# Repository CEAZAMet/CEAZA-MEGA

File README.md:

# CEAZA Mega   [![Badge License]][License]

*A reliable & expandable low power data <br>
logger for scientists, based on the Arduino.*

<br>
<br>

<div align = center>

</div>

<br>
<br>

## What It Is

Is a new simple, robust and expandable datalogger Arduino derivative board based in typical maker’s community integrations.  The board was designed and implemented taking into account requirements as low consumption, expandability and integration. Different tests where made so reliability in low temperatures and low energy needs are satisfied. 
Is expected that the scientific community can add this board to their tool set, as this board solves the energy problem and present an easy transition from handmade logger integrations.

CEAZA mega board integrate:
- ATMEGA2560 8-bit microcontroller
- Arduino mega 2560 bootloader for easy Arduino Ide compatibility
- A real time clock (RTC)
- A microSD card socket for data storage
- USB/Serial driver connected to UART0 for program as an Arduino mega or computer serial communication
- Serial RS-232 driver (connected to UART1) 
- Controlled high frequency (2MHz) step down switching regulator MP2451DT-LF-Z configured to deliver 5V and up to 600mA for external sensor
- Built in 10Kohm NTC thermistor for PCB temperature monitoring
- Power source system voltage monitor
- Terminal for direct connection with DS18B20 1-wire digittal temperature sensor
- 3 LEDs on board and external duplicate conection for two of those LEDs
- an ISCP terminal to program with external programer
- 3 expansion terminal for direct wires soldering or easy plug/unplug expansion boards for CEAZA MEGA

<br>

Furthermore, all integrated devices, except the main **MCU** <br>
uses a firmware controlled switched power supply in order <br>
to optimize de power consumption.

## Documentation

A comprehensive documentation for well understand, use <br>
or modify the **CEAZA MEGA** board is available in our Wiki. 

Additionally we share our schematic <br>
diagrams and Arduino example codes.

<br>
<br>

## Quickstart guide

1.  Connect a `6.5 - 14V` DC power supply.

2.  Connect the **CEAZA MEGA** main board to <br>
    the host PC with he mini-USB connector.

3.  Open the Arduino IDE.

4.  Select the Arduino Mega board <br>
    and the corresponding COM port.

5.  Open any of example sketches.

6.  Upload to the board.

<br>
<br>

## Contact & Support

For all kinds of inquiries, please contact me to <br>
my e-mail address: adrian.gallardo@ceaza.cl

<br>
<br>

## Contributing

You are welcome to contribute to the development <br>
or improvement of **CEAZA MEGA** hardware design <br>
or example application codes.

Feel free to submit a new pull request via **GitHub**.

<br>
<br>

## Academic Context

A paper with more details and performed tests was shown in **[DOI]**. 

<br>
<br>

## Disclaimer

Use **CEAZA MEGA** board and examples code at your own risk. <br>
We do not encourage any malicious use of our board.

<br>

<!----------------------------------------------------------------------------->

[Badge License]: https://img.shields.io/badge/License-MIT-yellow.svg?style=for-the-badge

[DOI]: http://doi.org/10.11591/ijres.v11.i2.pp175-187

[Preview]: Images/CM_PINOUT.PNG
[License]: LICENSE

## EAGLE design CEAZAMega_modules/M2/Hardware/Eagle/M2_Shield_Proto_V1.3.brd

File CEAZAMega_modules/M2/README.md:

# Welcome to CEAZA-M2!
Prototyping board for CEAZA MEGA system.

# What is the CEAZA-M2?
Is a prototyping board with a firmware controlled +5V dedicated step-down power supply and controlled Vin pin for CEAZA MEGA system.
The board give you access to some pins as a PCB breadboard format, ready to solder any module or device.
Furthermore the board have a duplicate I/O expansion terminals to give you direct access to any of its pins.
Whith CEAZA M2 board you can easyly integrate any device to CEAZA MEGA system without any other customized board.

## Documentation
A comprehensive documentation for well undertand, use or modify the CEAZA M2 board is available in our Wiki. In adition, we share with you the schematics diagrams, adns Arduino example codes.

## Quickstart guide
Plan your electronic conection to your device, solder the necesay wires to connect your devices in the M2 board.
Install the M2 board in the CEAZA MEGA's bottom, make certain connection throuhg the boards by three 2 x 10 pin header terminals is rigth. Plug the battery and solar panel cables in the respective board terminal. be careful to avoid swap both plugs, due they are the same type of terminals. Connect the CEAZA MEGA main board system to the host PC by mini-USB connector, open the Arduino ide software, select the Arduino Mega board and the correspondign COM port.
Open any of examples scketches and upload to the board.
### WARNING!
Be careful with your breadboard conections due exist a posibility of a shortcircuit of the power supply acces in the breadboard. 
A 1A PTC Resettable fuse is placed in the main electric supply to the board (VIN pin od I/O expansion terminal) for extra electric protection.

# Contact and support
For all kinds of inquiries, please contact me to my e-mail address: adrian.gallardo@ceaza.cl

# Contributing
You are welcome to contribute to the development or improvement of M2 hardware design or example application codes. Feel free to submit a new pull request via github.

# Academic Context

# Licensing

# Disclaimer
Use M2 board and examples code at your own risk. We do not encourage any malicious use of our board.

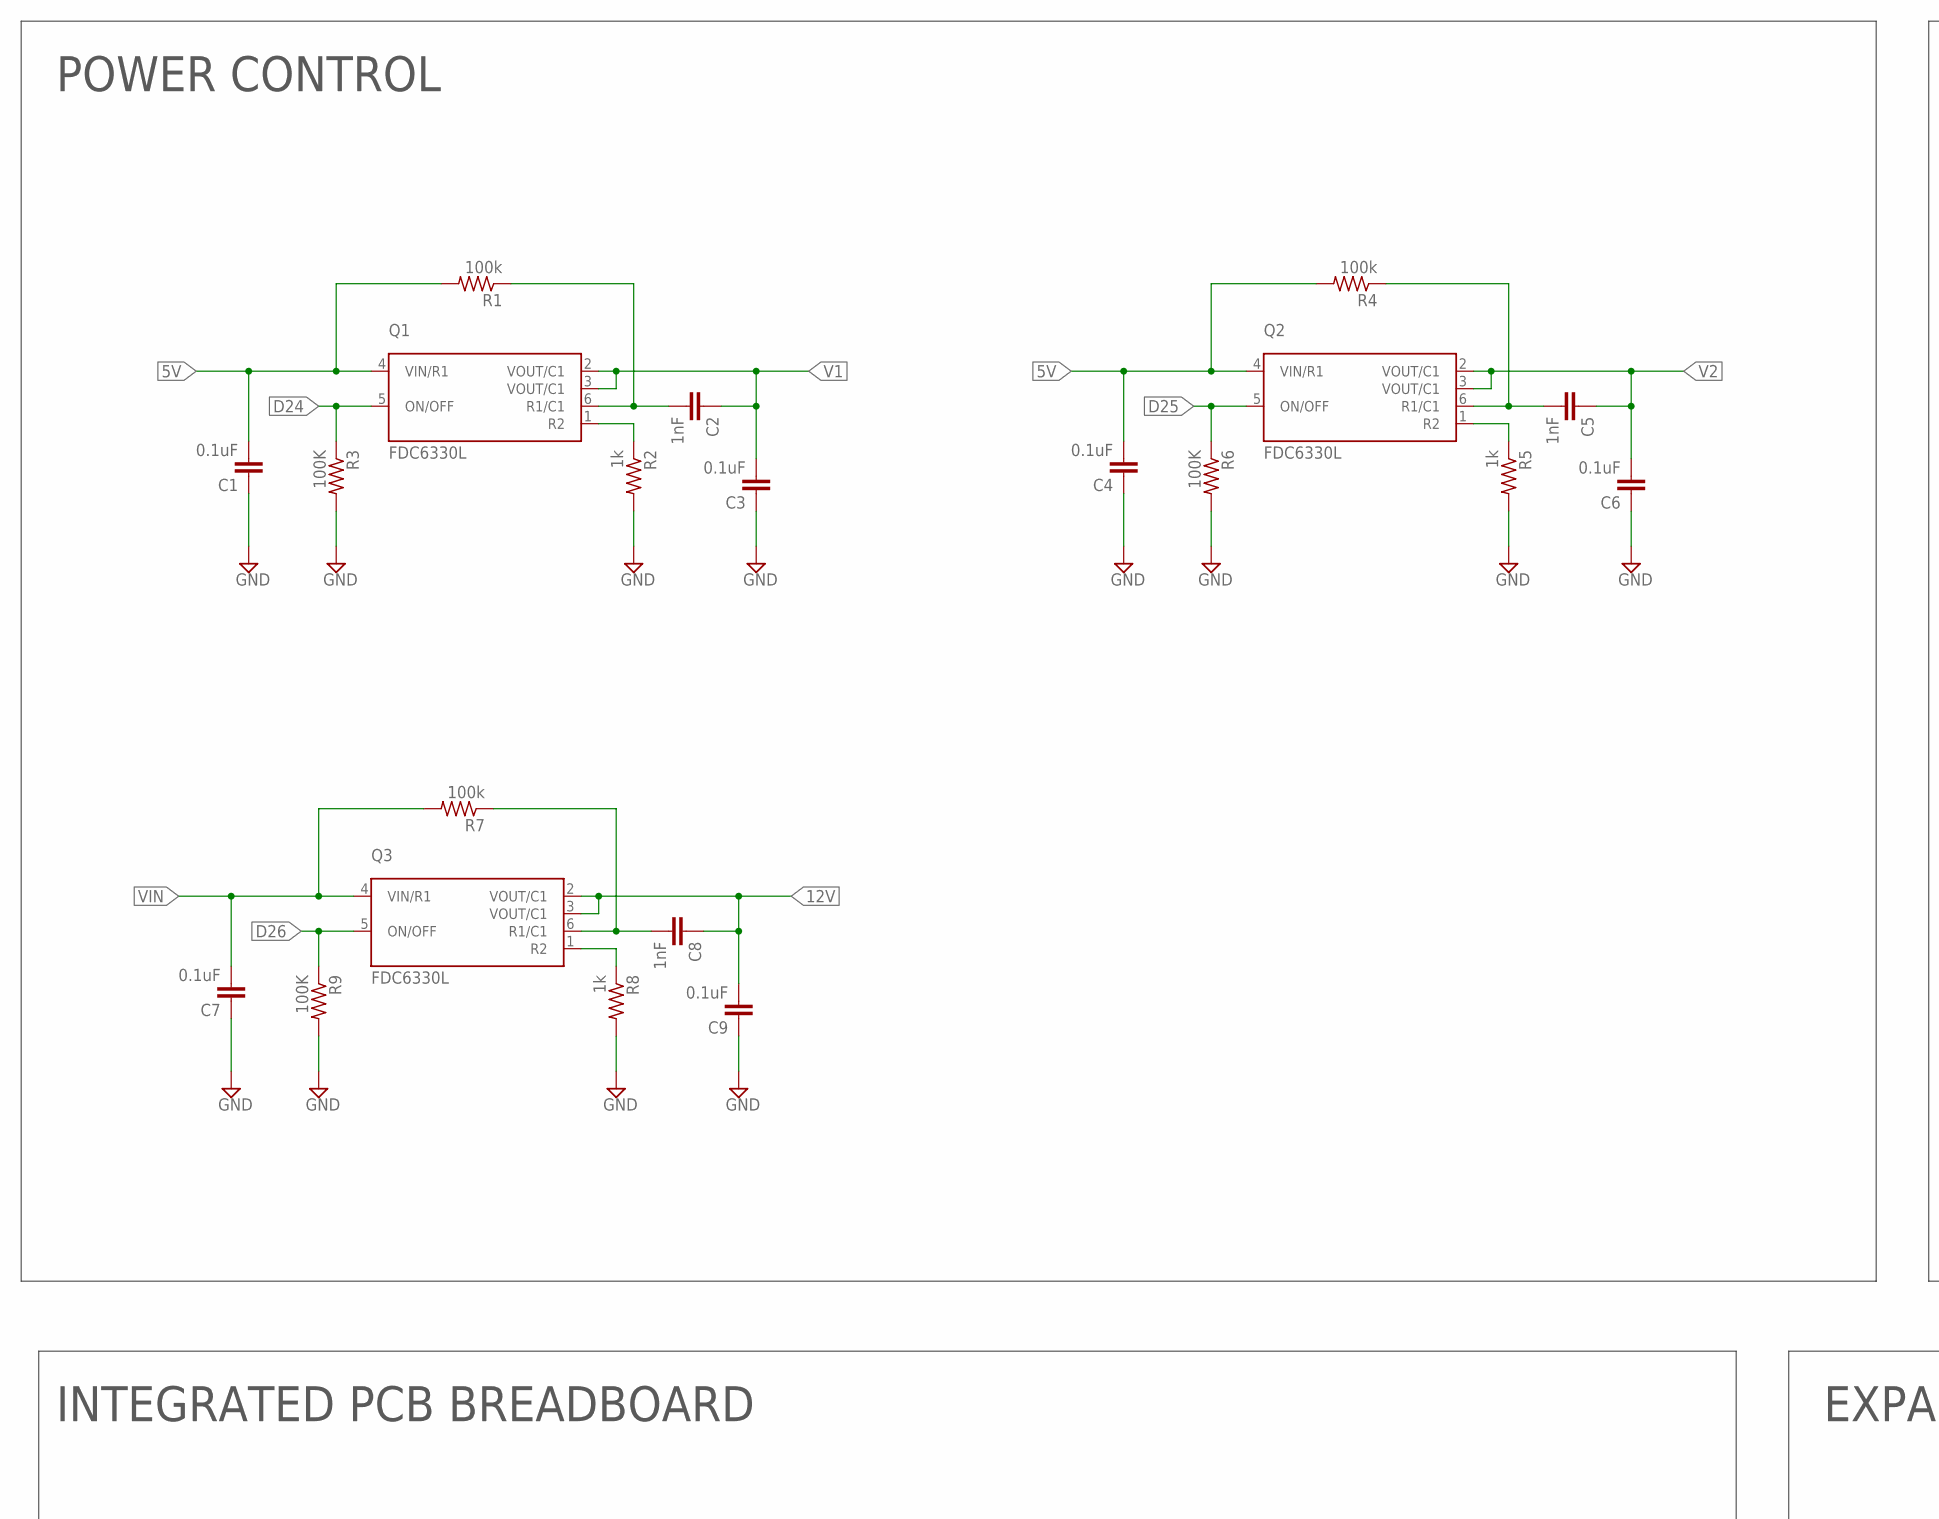
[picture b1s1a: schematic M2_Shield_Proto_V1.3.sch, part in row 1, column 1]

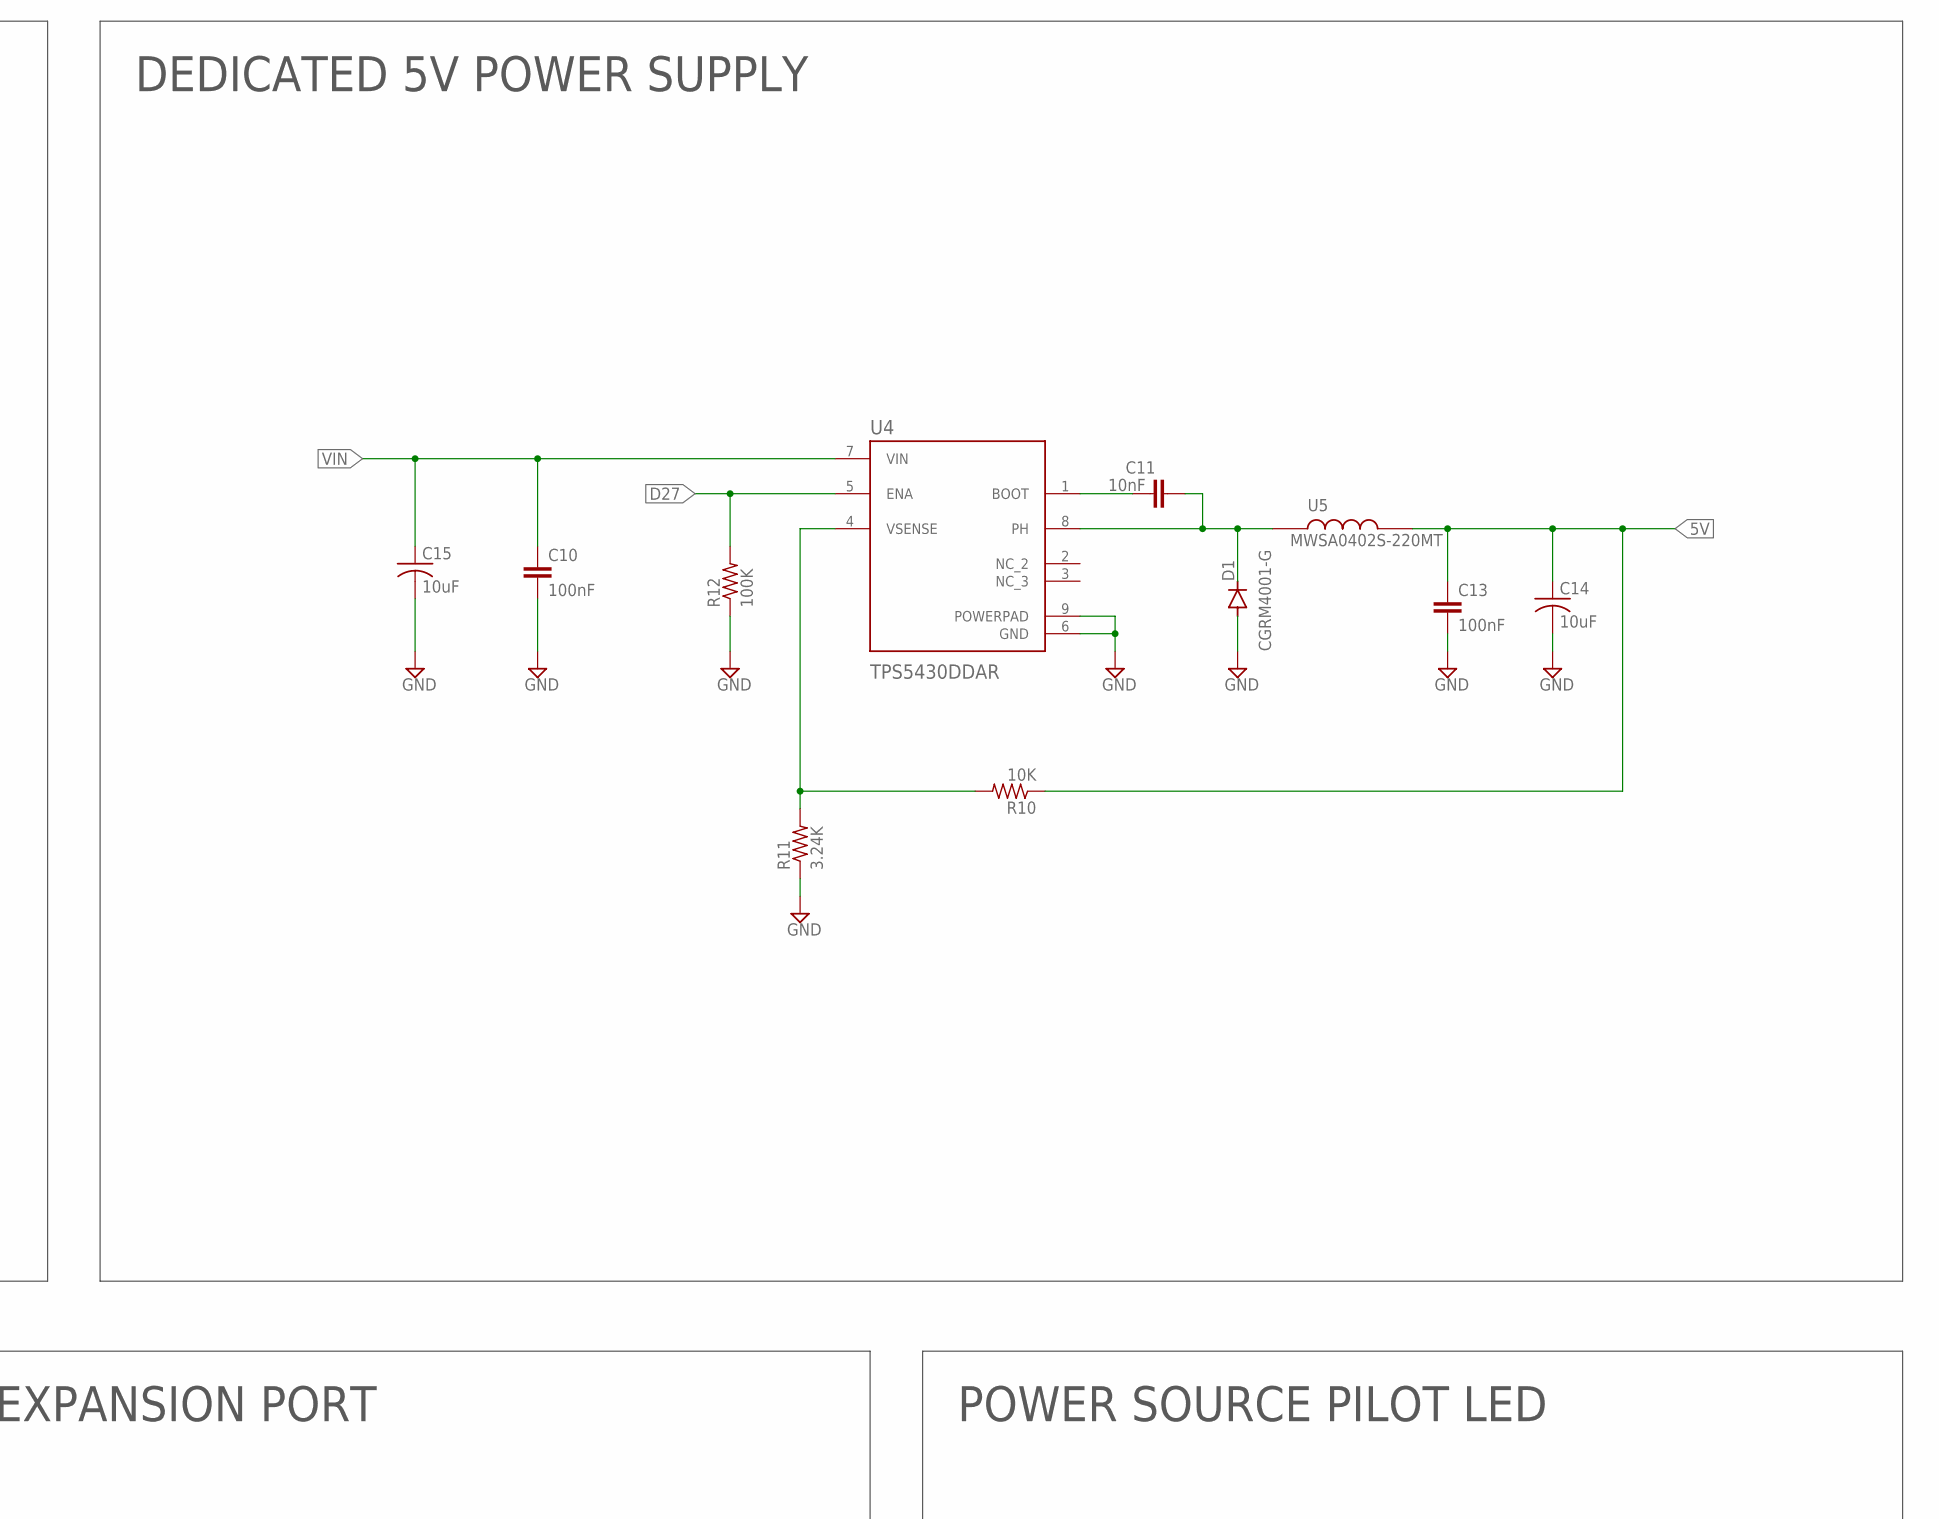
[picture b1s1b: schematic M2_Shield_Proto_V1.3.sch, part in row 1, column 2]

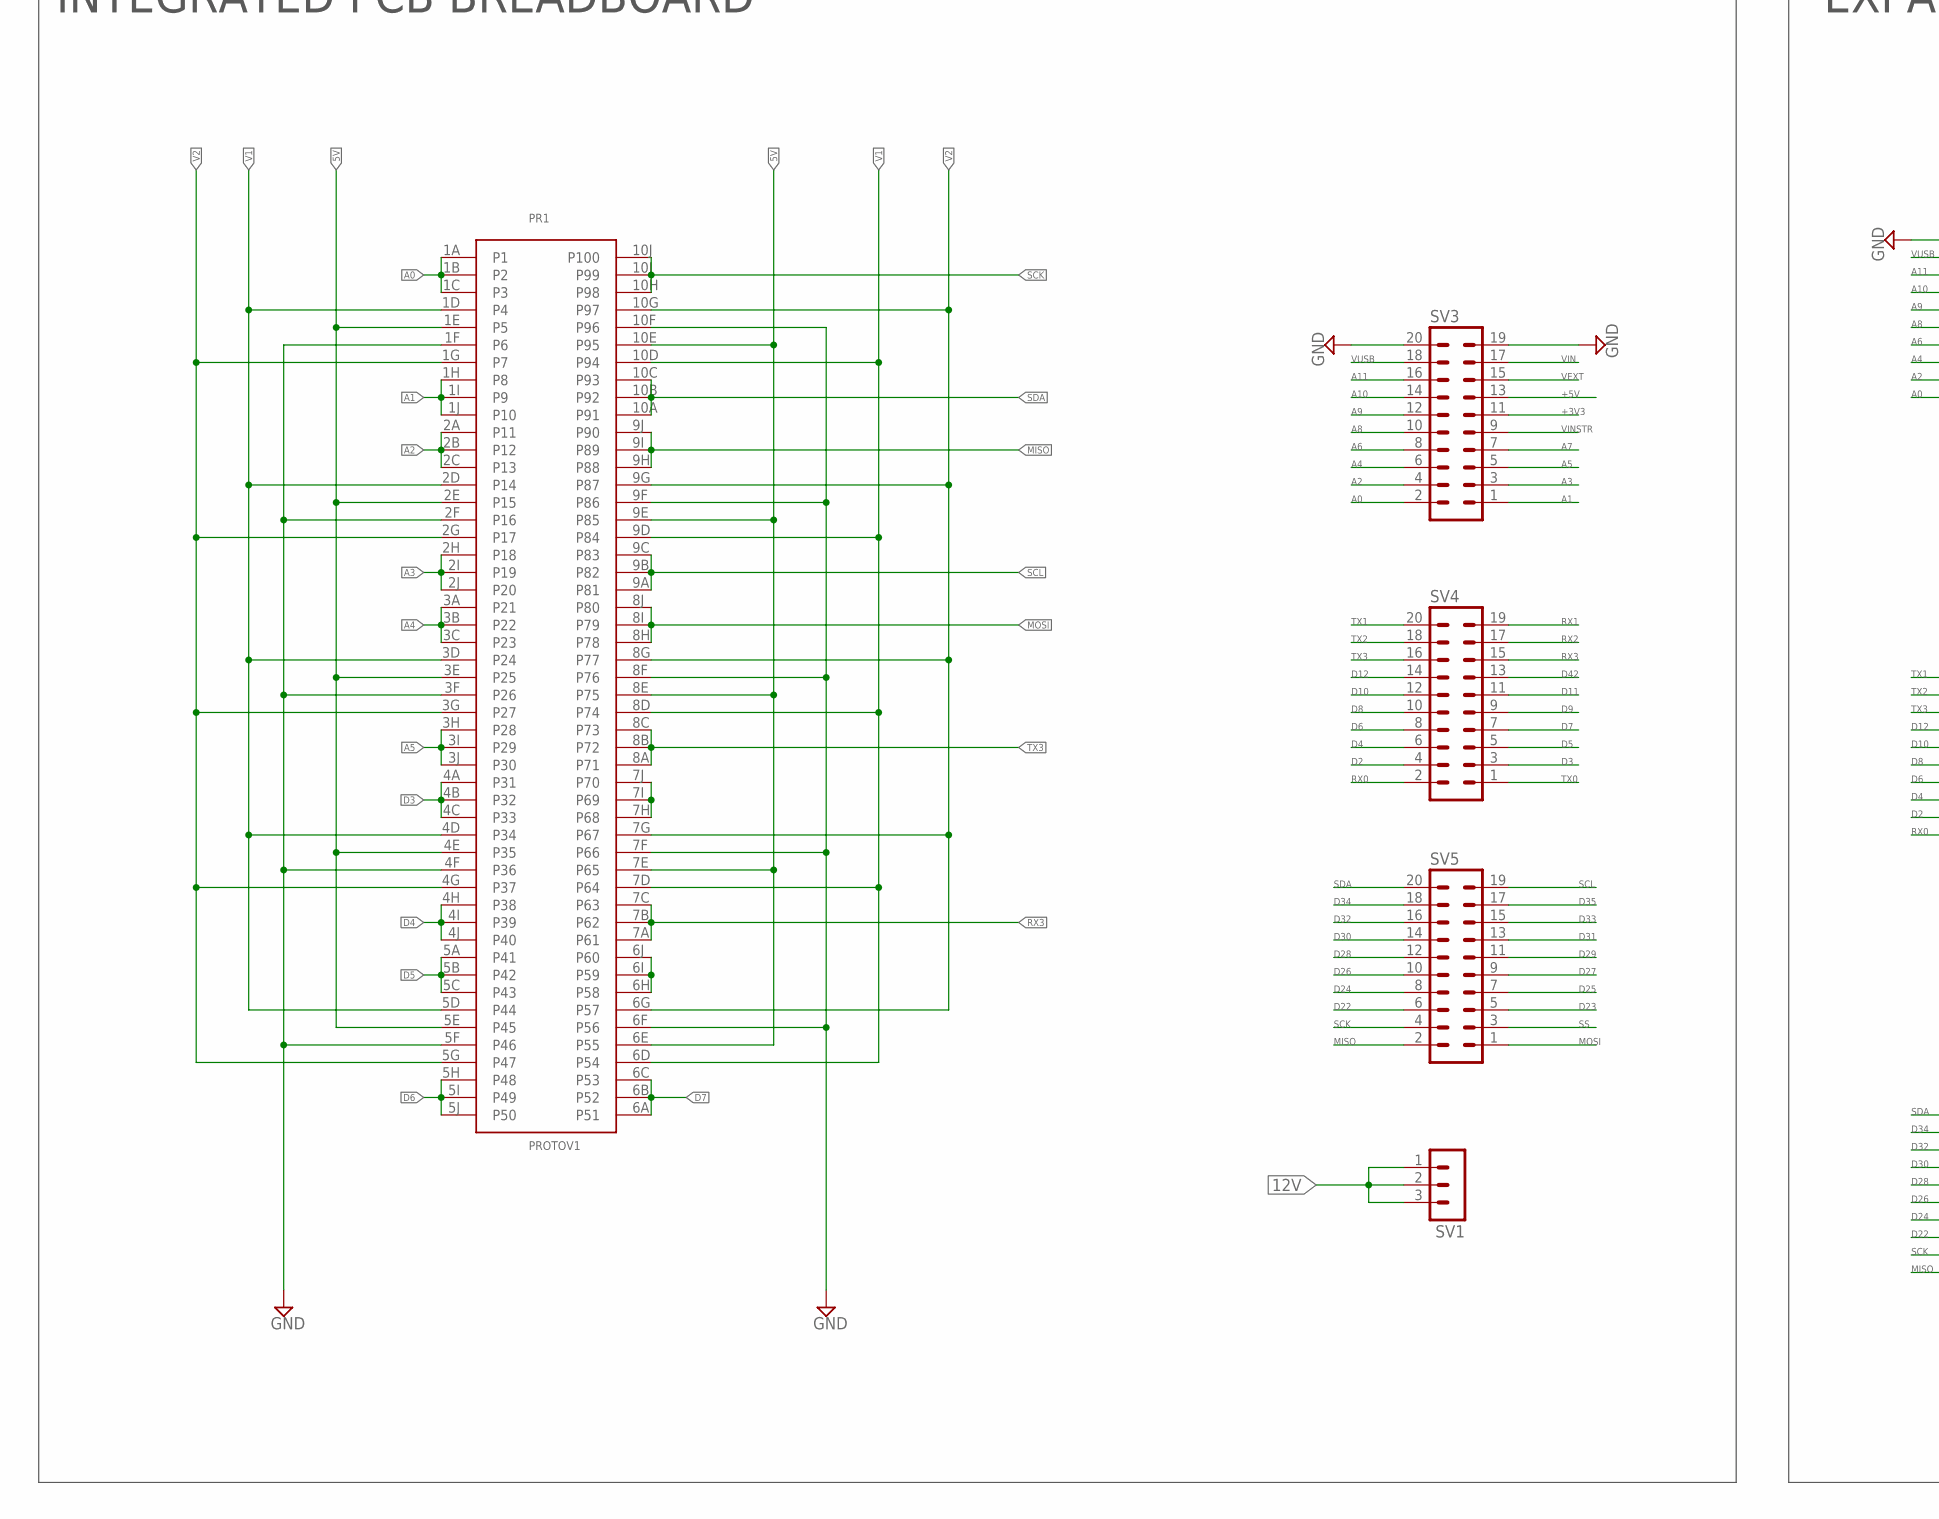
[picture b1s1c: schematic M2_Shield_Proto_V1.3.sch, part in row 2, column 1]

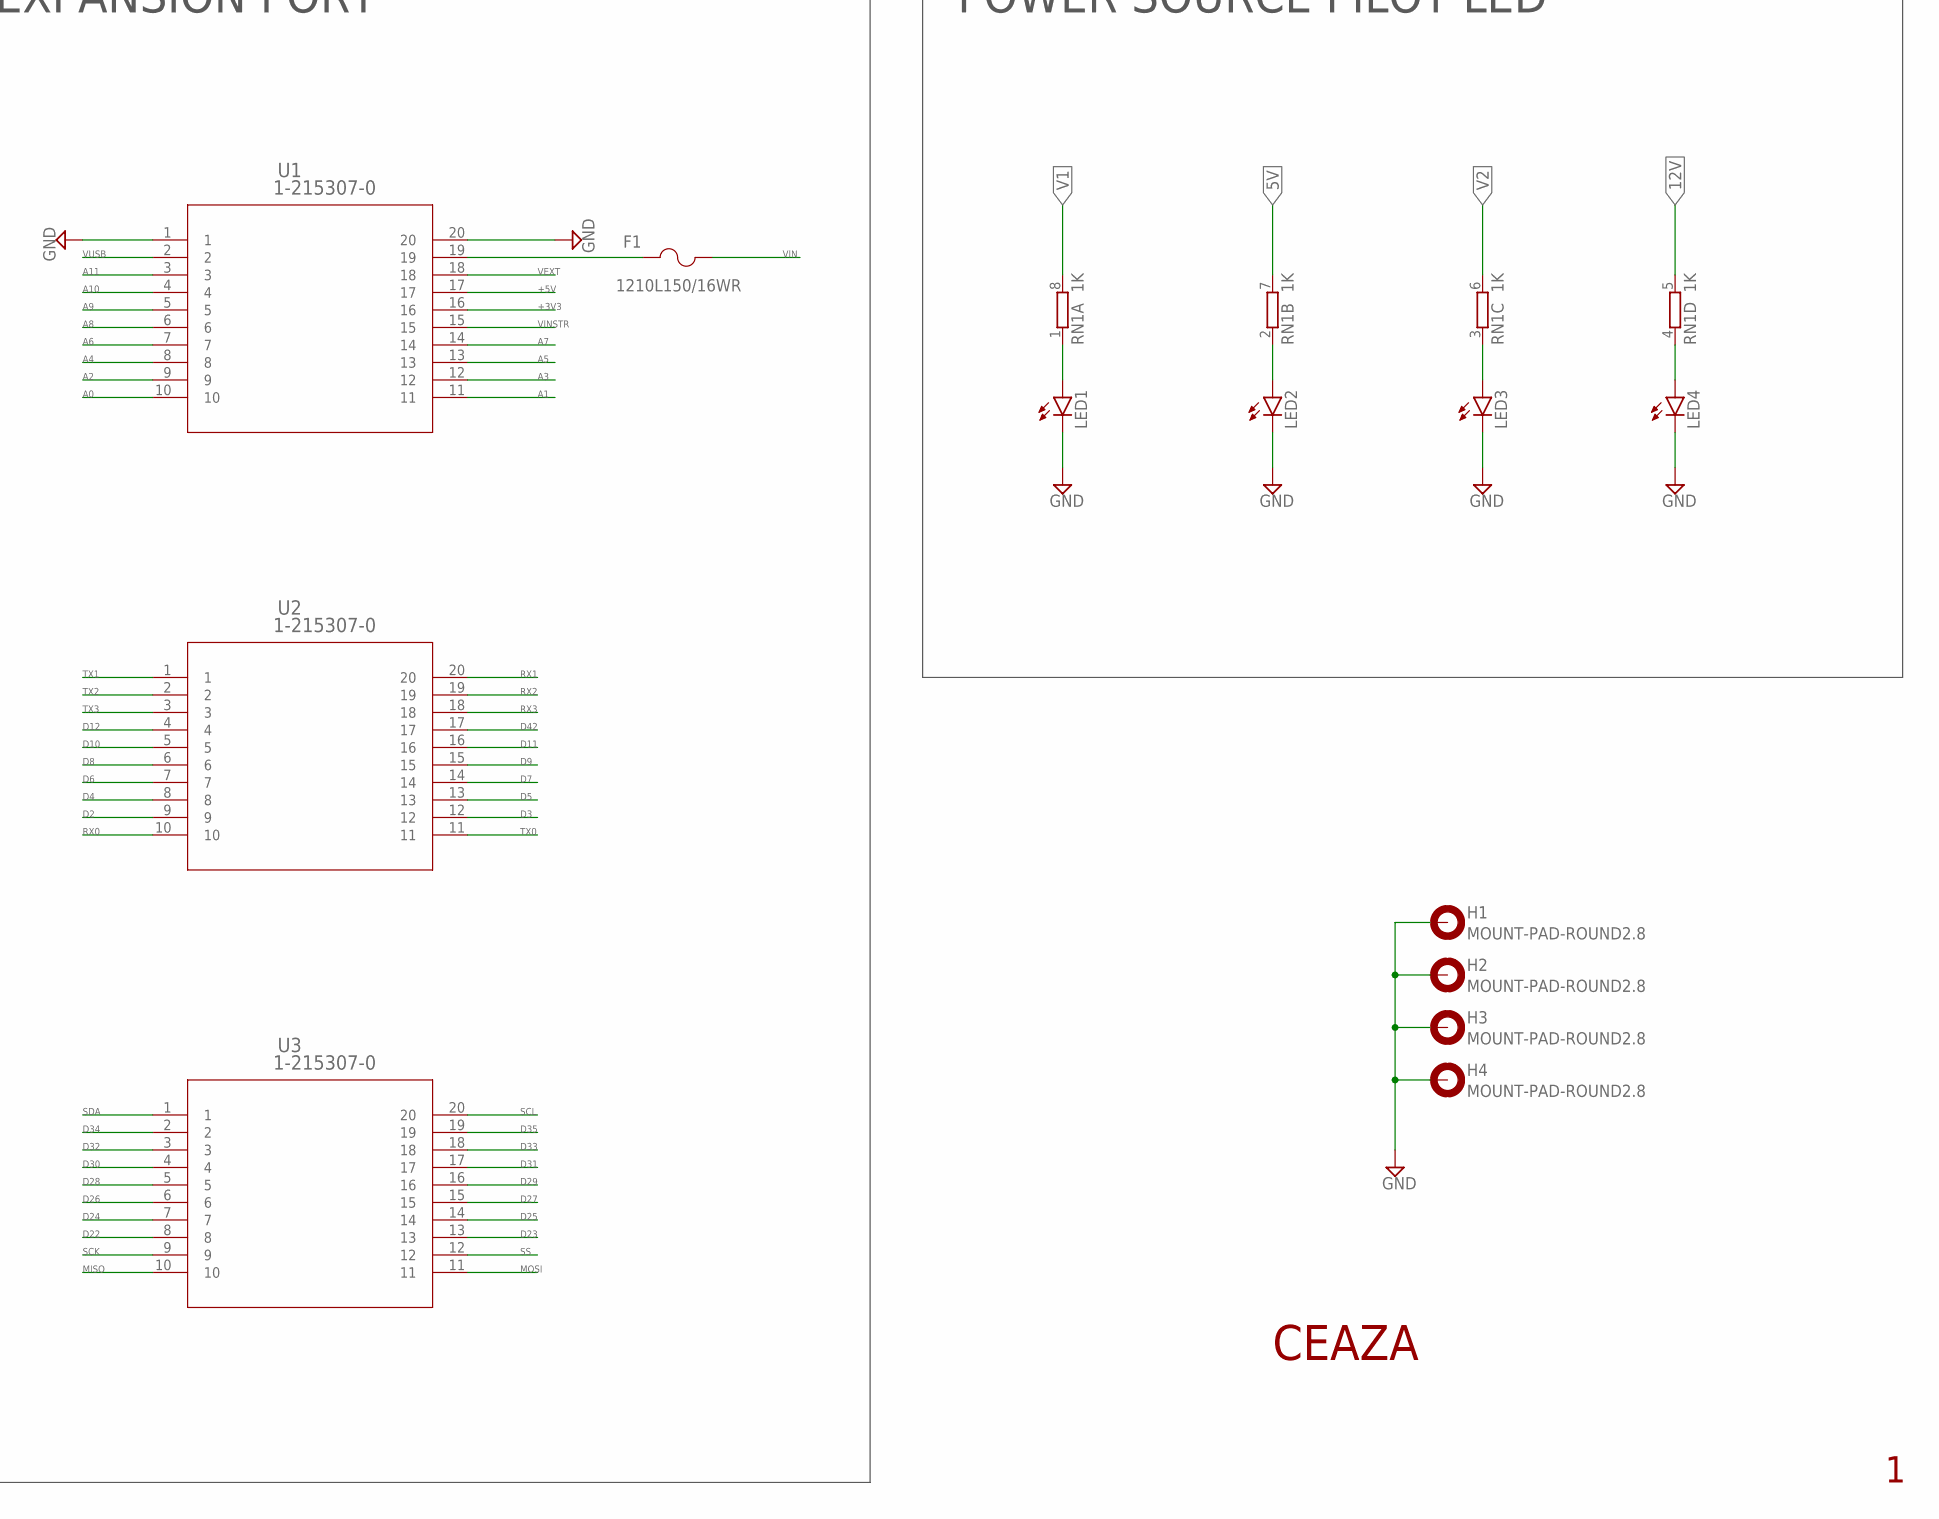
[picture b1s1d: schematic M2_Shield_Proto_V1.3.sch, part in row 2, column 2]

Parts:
C1, C3, C4, C6, C7, C9: 0.1uF; C0603
C2, C5, C8: 1nF; C0603
C10, C13: 100nF; C0603
C11: 10nF; C0603
C14, C15: 10uF; C0603
D1: CGRM4001-G; SOD-123_MINI-SMA
F1: 1210L150/16WR; 1210LSERIES
H1, H2, H3, H4: MOUNT-PAD-ROUND2.8; 2,8-PAD
LED1, LED2, LED3, LED4: LEDCHIP-LED0805; CHIP-LED0805
PR1: PROTOV1
Q1, Q2, Q3: FDC6330L; SOT95P280X110-6N
R1, R4, R7: 100k; R0603
R2, R5, R8: 1k; R0603
R3, R6, R9, R12: 100K; R0603
R10: 10K; R0603
R11: 3.24K; R0603
RN1: 1K; 0603-ARV
SV1: MA03-1
SV3, SV4, SV5: MA10-2
U1, U2, U3: 1-215307-0
U4: TPS5430DDAR; CONV_TPS5430DDAR
U5: MWSA0402S-220MT

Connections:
5V: C1.2, C4.2, C13.1, C14.1, PR1.1E (P5), PR1.2E (P15), PR1.3E (P25), PR1.4E (P35), PR1.5E (P45), PR1.6E (P55), PR1.7E (P65), PR1.8E (P75), PR1.9E (P85), PR1.10E (P95), Q1.4 (VIN/R1), Q2.4 (VIN/R1), R1.2, R4.2, R10.1, RN1.7 (2), U5.P$2
12V: C8.1, C9.2, Q3.2 (VOUT/C1), Q3.3 (VOUT/C1), RN1.5 (2), SV1.1, SV1.2, SV1.3
+3V3: SV3.11, U1.16
+5V: SV3.13, U1.17
A0: PR1.1A (P1), PR1.1B (P2), PR1.1C (P3), SV3.2, U1.10
A1: PR1.1H (P8), PR1.1I (P9), PR1.1J (P10), SV3.1, U1.11
A2: PR1.2A (P11), PR1.2B (P12), PR1.2C (P13), SV3.4, U1.9
A3: PR1.2H (P18), PR1.2I (P19), PR1.2J (P20), SV3.3, U1.12
A4: PR1.3A (P21), PR1.3B (P22), PR1.3C (P23), SV3.6, U1.8
A5: PR1.3H (P28), PR1.3I (P29), PR1.3J (P30), SV3.5, U1.13
A6: SV3.8, U1.7
A7: SV3.7, U1.14
A8: SV3.10, U1.6
A9: SV3.12, U1.5
A10: SV3.14, U1.4
A11: SV3.16, U1.3
D2: SV4.4, U2.9
D3: PR1.4A (P31), PR1.4B (P32), PR1.4C (P33), SV4.3, U2.12
D4: PR1.4H (P38), PR1.4I (P39), PR1.4J (P40), SV4.6, U2.8
D5: PR1.5A (P41), PR1.5B (P42), PR1.5C (P43), SV4.5, U2.13
D6: PR1.5H (P48), PR1.5I (P49), PR1.5J (P50), SV4.8, U2.7
D7: PR1.6A (P51), PR1.6B (P52), PR1.6C (P53), SV4.7, U2.14
D8: SV4.10, U2.6
D9: SV4.9, U2.15
D10: SV4.12, U2.5
D11: SV4.11, U2.16
D12: SV4.14, U2.4
D22: SV5.6, U3.8
D23: SV5.5, U3.13
D24: Q1.5 (ON/OFF), R3.1, SV5.8, U3.7
D25: Q2.5 (ON/OFF), R6.1, SV5.7, U3.14
D26: Q3.5 (ON/OFF), R9.1, SV5.10, U3.6
D27: R12.2, SV5.9, U3.15, U4.5 (ENA)
D28: SV5.12, U3.5
D29: SV5.11, U3.16
D30: SV5.14, U3.4
D31: SV5.13, U3.17
D32: SV5.16, U3.3
D33: SV5.15, U3.18
D34: SV5.18, U3.2
D35: SV5.17, U3.19
D42: SV4.13, U2.17
GND: C1.1, C3.1, C4.1, C6.1, C7.1, C9.1, C10.2, C13.2, C14.2, C15.2, D1.A, H1.B2,8, H2.B2,8, H3.B2,8, H4.B2,8, LED1.C, LED2.C, LED3.C, LED4.C, PR1.1F (P6), PR1.2F (P16), PR1.3F (P26), PR1.4F (P36), PR1.5F (P46), PR1.6F (P56), PR1.7F (P66), PR1.8F (P76), PR1.9F (P86), PR1.10F (P96), R2.2, R3.2, R5.2, R6.2, R8.2, R9.2, R11.1, R12.1, SV3.19, SV3.20, U1.1, U1.20, U4.6 (GND), U4.9 (POWERPAD)
MISO: PR1.9H (P88), PR1.9I (P89), PR1.9J (P90), SV5.2, U3.10
MOSI: PR1.8H (P78), PR1.8I (P79), PR1.8J (P80), SV5.1, U3.11
unnamed: C11.1, U4.1 (BOOT)
unnamed: LED1.A, RN1.1
unnamed: LED2.A, RN1.2 (1)
unnamed: LED3.A, RN1.3 (1)
unnamed: LED4.A, RN1.4 (1)
unnamed: C11.2, D1.C, U4.8 (PH), U5.P$1
unnamed: C2.2, Q1.6 (R1/C1), R1.1
unnamed: Q1.1 (R2), R2.1
unnamed: C5.2, Q2.6 (R1/C1), R4.1
unnamed: Q2.1 (R2), R5.1
unnamed: PR1.6H (P58), PR1.6I (P59), PR1.6J (P60)
unnamed: PR1.7H (P68), PR1.7I (P69), PR1.7J (P70)
unnamed: R10.2, R11.2, U4.4 (VSENSE)
unnamed: C8.2, Q3.6 (R1/C1), R7.1
unnamed: Q3.1 (R2), R8.1
unnamed: F1.1, U1.19
RX0: SV4.2, U2.10
RX1: SV4.19, U2.20
RX2: SV4.17, U2.19
RX3: PR1.7A (P61), PR1.7B (P62), PR1.7C (P63), SV4.15, U2.18
SCK: PR1.10H (P98), PR1.10I (P99), PR1.10J (P100), SV5.4, U3.9
SCL: PR1.9A (P81), PR1.9B (P82), PR1.9C (P83), SV5.19, U3.20
SDA: PR1.10A (P91), PR1.10B (P92), PR1.10C (P93), SV5.20, U3.1
SS: SV5.3, U3.12
TX0: SV4.1, U2.11
TX1: SV4.20, U2.1
TX2: SV4.18, U2.2
TX3: PR1.8A (P71), PR1.8B (P72), PR1.8C (P73), SV4.16, U2.3
V1: C2.1, C3.2, PR1.1D (P4), PR1.2D (P14), PR1.3D (P24), PR1.4D (P34), PR1.5D (P44), PR1.6D (P54), PR1.7D (P64), PR1.8D (P74), PR1.9D (P84), PR1.10D (P94), Q1.2 (VOUT/C1), Q1.3 (VOUT/C1), RN1.8 (2)
V2: C5.1, C6.2, PR1.1G (P7), PR1.2G (P17), PR1.3G (P27), PR1.4G (P37), PR1.5G (P47), PR1.6G (P57), PR1.7G (P67), PR1.8G (P77), PR1.9G (P87), PR1.10G (P97), Q2.2 (VOUT/C1), Q2.3 (VOUT/C1), RN1.6 (2)
VEXT: SV3.15, U1.18
VIN: C7.2, C10.1, C15.1, F1.2, Q3.4 (VIN/R1), R7.2, SV3.17, U4.7 (VIN)
VINSTR: SV3.9, U1.15
VUSB: SV3.18, U1.2

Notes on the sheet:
DEDICATED 5V POWER SUPPLY
POWER CONTROL
INTEGRATED PCB BREADBOARD
EXPANSION PORT
POWER SOURCE PILOT LED
CEAZA

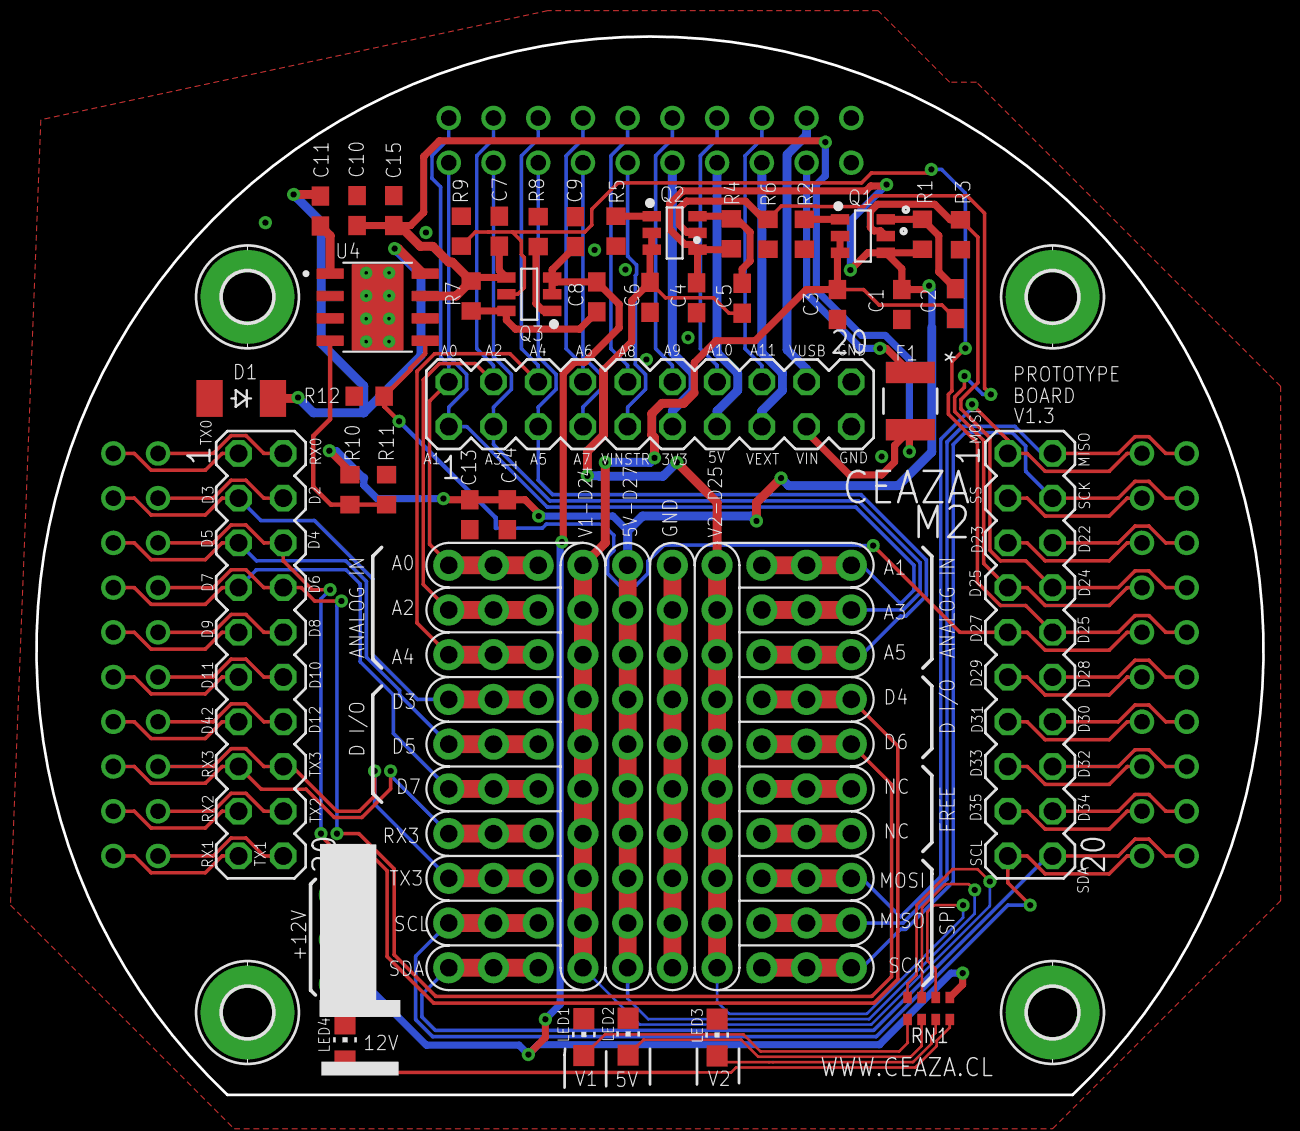
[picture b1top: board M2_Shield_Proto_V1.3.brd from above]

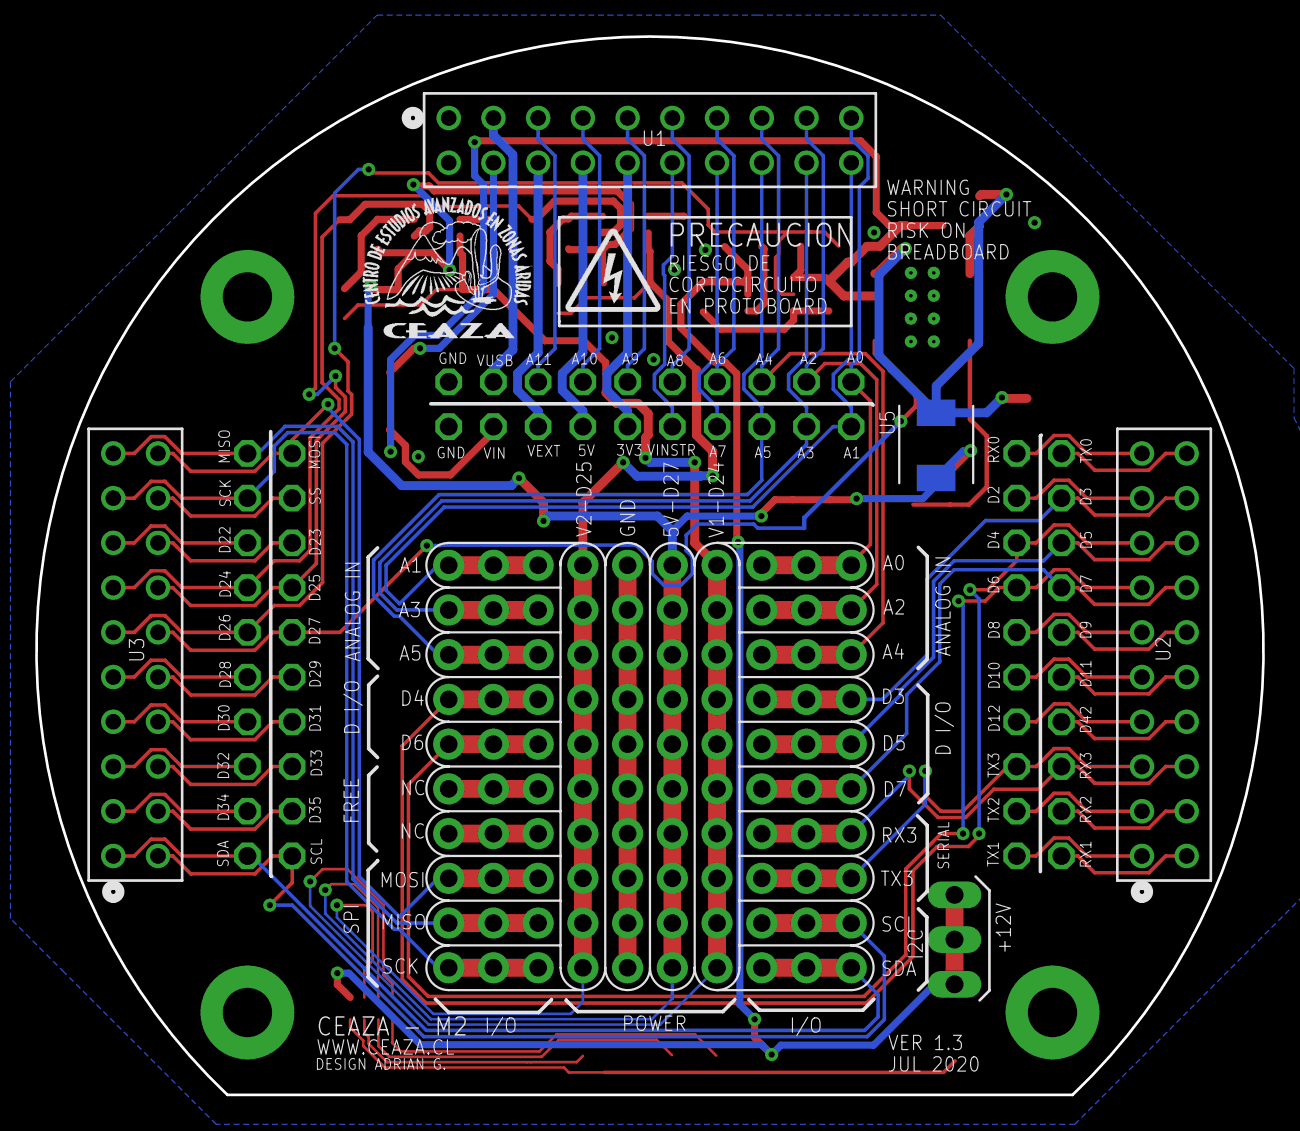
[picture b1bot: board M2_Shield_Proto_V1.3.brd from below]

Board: 2 copper layers, 69.7 x 60.1 mm, 50 parts (4 on the bottom side), 79 nets.

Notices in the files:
parts and their libraries:
SparkFun-Connectors: Licensing: Creative Commons ShareAlike 4.0 International - https://creativecommons.org/licenses/by-sa/4.0
COPYRIGHT: Copyright (C) 2018 Accelerated Designs. All rights reserved
